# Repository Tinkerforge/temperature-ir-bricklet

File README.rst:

Temperature IR Bricklet
=======================

This repository contains the firmware source code and the hardware design
files. The documentation generator configs can be found at
https://github.com/Tinkerforge/generators

Repository Content
------------------

software/:
 * examples/: Examples for all supported languages
 * build/: Compiled files
 * src/: Source code of firmware
 * Makefile: Makefile to build project

hardware/:
 * Contains KiCad project files and additionally schematics as PDF

datasheets/:
 * Contains datasheets for sensors and complex ICs that are used

Hardware
--------

The hardware is designed with the open source EDA Suite KiCad
(http://www.kicad.org). Before you are able to open the files,
you have to install the Tinkerforge kicad-libraries
(https://github.com/Tinkerforge/kicad-libraries). You can either clone
them directly in hardware/ or clone them in a separate folder and
symlink them into hardware/
(ln -s kicad_path/kicad-libraries project_path/hardware). After that you
can open the .pro file in hardware/ with KiCad and from there view and
modify the schematics and the PCB layout.

Software
--------

If you want to do your own Brick/Bricklet firmware development we highly
recommend that you use our build environment setup script and read the
tutorial (https://www.tinkerforge.com/en/doc/Tutorials/Tutorial_Build_Environment/Tutorial.html).

To compile the C code we recommend you to install the newest GNU Arm Embedded
Toolchain (https://launchpad.net/gcc-arm-embedded/+download).
You also need to install bricklib (https://github.com/Tinkerforge/bricklib)
and brickletlib (https://github.com/Tinkerforge/brickletlib).

You can either clone it directly in software/src/ or clone it in a
separate folder and symlink it into software/src/
(ln -s bricklib_path/bricklib project_path/software/src/ and
ln -s brickletlib_path/brickletlib project_path/software/src/).
Finally make sure to have CMake installed
(http://www.cmake.org/cmake/resources/software.html).

After that you can build the firmware by invoking make in software/.
The firmware (.bin) can then be found in software/build/ and uploaded
with brickv (click button "Flashing" on start screen).

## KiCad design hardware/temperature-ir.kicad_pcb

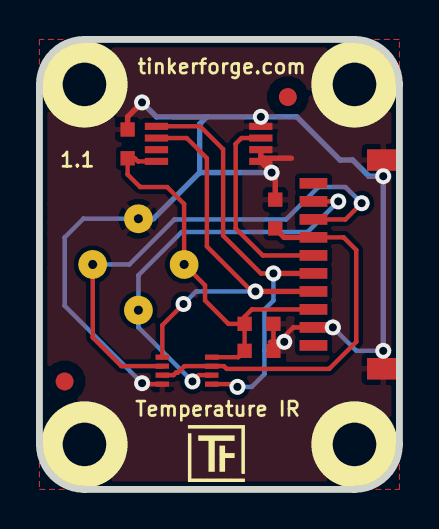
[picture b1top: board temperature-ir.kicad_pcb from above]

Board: 2 copper layers, 20.0 x 25.0 mm, 17 parts (0 on the bottom side), 8 nets.

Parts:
C1, C2, C3: 100nF; C0603
Fiducial_Mark: VAL**; Fiducial_Mark
Fiducial_Mark#2: VAL**; Fiducial_Mark
P1: CON-SENSOR
R1: 10k; R0603
Ref**: Val**; Logo_31x31
U1: NC7WB66K8X; VSSOP8
U2: MLX90614; TO-39
U3: M24C64; TSSOP8
U4, U5, U6, U7: DRILL; DRILL_NP
VAL: CE_5mm
VAL#2: WEEE_7mm

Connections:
GND: C1.2, C2.2, C3.1, P1.2, P1.EP, R1.2, U1.4, U2.4, U3.1, U3.2, U3.4
unnamed: P1.6, U3.3
unnamed: P1.7, R1.1, U1.3, U1.7
SCL: P1.4, U1.1, U3.6
SCL2: P1.8, U1.2, U2.1
SDA: P1.5, U1.5, U3.5
SDA2: P1.9, U1.6, U2.2
VCC: C1.1, C2.1, C3.2, P1.3, U1.8, U2.3, U3.8

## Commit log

2011-08-25 initial hardware source commit
2011-08-25 add project description
2011-09-13 add java bindings and examples
2011-09-14 limit line length of java examples to 100 characters
2011-09-23 Add C# examples and bindings
2011-10-05 Remove Bindings and IP Connection (these are generated and they change too often) and rename bindings to examples
2011-10-05 add tinkerforge package to python imports
2011-10-06 remove faulty gcc commandline invocation
2011-10-06 add firmware version and name
2011-12-10 use O2, otherwise there is not enough space
2012-02-14 add compatability for different tick types
2012-02-15 Add changelog
2012-02-24 Add support for more then one Temp IR at once
2012-04-25 Unify capitalization of "IP connection"
2012-05-09 Add PHP examples
2012-05-11 Fix signed/unsigned mismatch in C example
2012-05-14 java: Remove unnecessary new String(...) calls
2012-05-24 Remove '-' from device name
2012-05-25 Add Ruby examples
2012-06-05 Fix register_callback syntax error in Ruby examples on Windows
2012-06-12 Use correct term 'Bricklet' in example code error message
2012-06-12 Prefer IPConnection destroy over join_thread
2012-07-01 Add generate_makefile.bat for windows
2012-07-25 Add Delphi examples
2012-08-08 delphi: Add comment about UID
2012-10-24 Make cmake find the correct objcopy binary
    On some systems cmake uses the wrong objcopy binary, tell it to use
    the correct one.
2012-11-13 Support for protocol 2.0
2012-11-29 Make examples compatible to Protocol V2.0
2012-11-29 Make Ruby examples Protocol 2.0 compatible
2012-11-29 Make C examples Protocol 2.0 compatible
2012-11-29 Make Java examples Protocol 2.0 compatible
2012-11-29 Make PHP examples Protocol 2.0 compatible
2012-11-29 Make Delphi/Pascal examples Protocol 2.0 compatible
2012-11-30 delphi: Remove unnecessary parentheses and call destructor again
2012-12-05 Add protocol 2.0 compatability to C# bindings
2012-12-06 Fix C examples
2012-12-11 Avoid g++ warnings about missing casts in C examples
2012-12-13 Unify PHP example
2012-12-21 Add .gitignore
2013-01-08 Use new mutex_isr API
2013-01-09 Use specific device object for callbacks
2013-01-17 Make Java examples compatible to new listener approach
2013-01-28 Update outdated comment in Java example
2013-02-07 Use IPconnection disconnect explicitly in examples
2013-02-14 Fix debounce period in C# water boiling example
2013-02-18 Add Visual Basic .NET examples
2013-05-15 Don't send threshold callback twice
    Fixed in brickletlib.
2013-08-14 Add shell examples
2013-08-21 windows: Don't trigger a build in generate_makefile.bat
    Also use normal make instead of a special named one.
2013-12-19 Fix wrong length for GetDebounce packet (through brickletlib)
2014-01-06 Add static assert for BrickContext size
2014-01-10 Add Perl examples
2014-01-15 php: Use const for constant values
2014-02-07 Add Mathematica examples
2014-02-10 perl: fixed namespace
2014-02-12 javascript: add examples
2014-02-18 javascript: examples fixed
2014-02-20 javascript: adding html exmaples
2014-02-24 javascript: port 4280, startExample()
2014-02-28 javascript: Break long lines and cleanup whitespace
2014-03-05 Add LabVIEW examples
2014-03-06 labview: Add examples in LV2010 format
2014-03-26 matlab: add examples
2014-03-27 Go back to synchronous communication because of rare problems with FreeRTOS
2014-04-02 java: Unify constants style
2014-04-02 perl: Unify print style
2014-04-17 matlab: Adapt examples to new callback style
2014-04-17 matlab: Add parentheses to make pygments happy
2014-07-15 java: Replace System.console() usage with an Eclipse compatible pattern
2014-12-02 Use ReadLine instead of ReadKey for C# example
2014-12-30 Make sure that select line is pulled, so that I2C switch on Master Brick 2.1 works properly
2015-02-13 vbnet: Use ReadLine instead of ReadKey
    Because ReadKey doesn't work with a pipe as stdin on the RED Brick.
2015-03-02 windows: Stop cmake from searching for mingw32-make.exe
    Using MinGW Makefiles as generator makes cmake search for mingw32-make.exe
    which might not be installed because GnuWin32's make.exe is used instead.
2015-03-26 update to current hardware version
2015-04-09 c: Whitespace
2015-06-24 javascript: Clean up output creation
2015-06-29 octave: Handle short difference between Octave 3.6 and 3.8
    In Octave 3.6 a short is not automatically handled as a number.
2015-07-25 Make JavaScript browser example textarea readonly
2015-07-27 Cleanup C/C++, C#, Java, Python and Ruby examples
2015-07-28 Whitespace
2015-07-29 Reformat changelog
2015-08-07 Use full device class name in Python examples
2015-08-12 Fix minor warnings in C/C++ examples
2015-08-14 Cleanup Delphi examples
2015-08-18 Cleanup VB.NET examples
2015-08-19 Cleanup Perl examples
2015-09-09 Duplicate cmake call to fix bug during cmake creation
2015-09-30 Generator based example cleanup
2015-11-12 matlab: Fix callback handling for R2014a
    http://undocumentedmatlab.com/blog/matlab-callbacks-for-java-events-in-r2014a
2015-11-25 Include date and commit into changelog
2015-11-30 vbnet: Break long line
2016-05-18 c: Add missing device destroy call
2016-07-01 Make the change UID comment more explicit
2017-04-13 csharp: Adapt example
2017-04-21 shell: Adapt example
2017-06-02 octave: Use javaObject instead of deprecated java_new
2017-08-04 Add 3d information (*.step & *.FCStd)
2017-08-04 Add 3d model (*.step & *.FCStd)
2017-10-26 fix mlx90614 text size
2017-11-30 Update examples from generator
2017-12-07 mathematica: Also generate .nb files
2018-02-01 Fix path for 3d model of the IR sensor
2018-02-02 Update examples
2018-02-19 javascript: Close div tag correctly
2018-02-20 Cleanup KiCad libraries config
    Ensure LibDir=kicad-libraries and LibName1=tinkerforge.
    Remove special library.
2018-05-25 perl: Use strict in examples
2018-06-05 labview: Fix example file names
2018-07-11 Add Makefile with docker support
2018-07-11 Remove obsolete generate_makefile scripts
2018-07-11 Update directory structure and build instructions
2018-09-14 vbnet: Fix typo in comment
2018-11-06 Add rust examples
2018-11-07 rust: Accept host names for ip connection, fix naming inconsistencies
2018-11-07 rust: Rename callback receivers.
2018-12-14 Add go examples.
2018-12-14 go: Fix printf parameters.
2018-12-18 go: Change import path.
2018-12-18 go: Change import path again.
2018-12-20 rust: Reformat examples.
2019-01-24 mqtt: Add examples.
2019-01-24 mqtt: Fix example header.
2019-01-24 mqtt: Remove executable bit in example permissions.
2019-01-24 go: Minor example fixes.
2019-01-24 mqtt: Minor example fixes.
2019-03-28 mqtt: Fix whitespace.
2019-08-22 c: Adapt to bindings changes
2020-01-13 examples: Use python3 input instead of python2 raw_input.
2020-01-13 examples: mqtt: Remove trailing whitespace.
2020-04-07 examples: rust: Always block when calling bindings functions.
2020-04-14 mqtt: Fix device name format
2021-10-25 Update KiCad link
    https://www.kicad.org/blog/2021/10/Avoid-links-to-former-kicad-domain/
2022-07-06 Add license files.

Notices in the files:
hardware/temperature-ir.kicad_pcb:
Licensed under CERN OHL v.1.1
Copyright (©) 2011, B.Nordmeyer
Copyright Tinkerforge GmbH 2011.
This documentation describes Open Hardware and is licensed under the
CERN OHL v. 1.1.
